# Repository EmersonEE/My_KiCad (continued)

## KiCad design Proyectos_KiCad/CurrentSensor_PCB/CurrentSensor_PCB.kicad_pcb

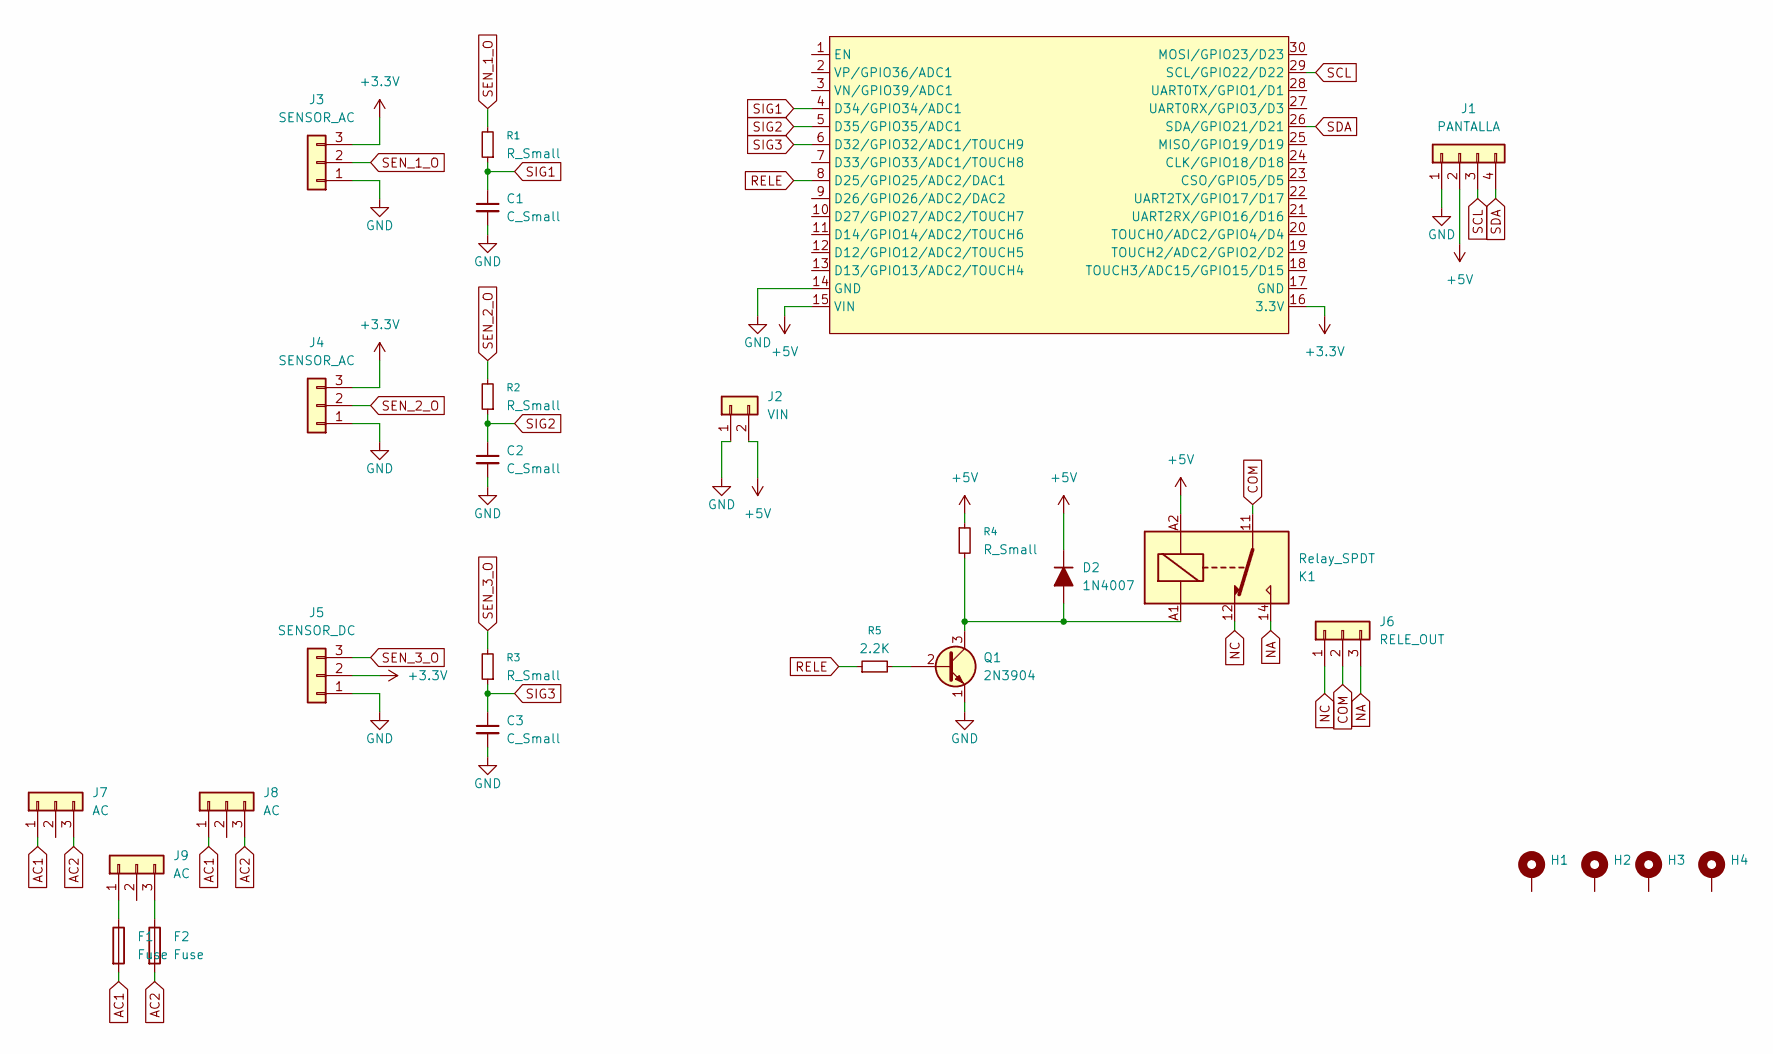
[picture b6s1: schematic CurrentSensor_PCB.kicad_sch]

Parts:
C1, C2, C3: C_Small; C_Disc_D3.8mm_W2.6mm_P2.50mm
D2: 1N4007; D_DO-41_SOD81_P7.62mm_Horizontal
F1, F2: Fuse; Fuseholder5x20_horiz_open_inline_Type-I
H1, H2, H3, H4: MountingHole_3.2mm_M3_Pad_Via
J1: PANTALLA; Molex_KK-254_AE-6410-04A_1x04_P2.54mm_Vertical
J2: VIN; TerminalBlock_Phoenix_MKDS-1,5-2-5.08_1x02_P5.08mm_Horizont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
J3, J4: SENSOR_AC; Molex_KK-254_AE-6410-03A_1x03_P2.54mm_Vertical
J5: SENSOR_DC; PinHeader_1x03_P2.54mm_Vertical
J6: RELE_OUT; TerminalBlock_Phoenix_MKDS-1,5-3-5.08_1x03_P5.08mm_Horizont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
J7, J8, J9: AC; TerminalBlock_Phoenix_MKDS-1,5-3-5.08_1x03_P5.08mm_Horizont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
K1: Relay_SPDT; Relay_SPDT_Finder_36.11
Q1: 2N3904; TO-92_Inline_Wide_EBC
R1, R2, R3, R4: R_Small; 2.2K
R5: 2.2K
U1: ESP32_DevKit_V1_DOIT; ESP32_DEVKIT_V1_E32

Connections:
+3.3V: J3.3, J4.3, J5.2, U1.16 (3.3V)
+5V: D2.1 (K), J1.2, J2.2, K1.A2, R4.1, U1.15 (VIN)
AC1: F1.2, J7.1, J8.1
AC2: F2.2, J7.3, J8.3
COM: J6.2, K1.11
GND: C1.2, C2.2, C3.2, J1.1, J2.1, J3.1, J4.1, J5.1, Q1.1 (E), U1.14 (GND)
NA: J6.3, K1.14
NC: J6.1, K1.12
unnamed: D2.2 (A), K1.A1, Q1.3 (C), R4.2
unnamed: F1.1, J9.1
unnamed: F2.1, J9.3
unnamed: Q1.2 (B), R5.2
RELE: R5.1, U1.8 (D25/GPIO25/ADC2/DAC1)
SCL: J1.3, U1.29 (SCL/GPIO22/D22)
SDA: J1.4, U1.26 (SDA/GPIO21/D21)
SEN_1_O: J3.2, R1.2
SEN_2_O: J4.2, R2.2
SEN_3_O: J5.3, R3.2
SIG1: C1.1, R1.1, U1.4 (D34/GPIO34/ADC1)
SIG2: C2.1, R2.1, U1.5 (D35/GPIO35/ADC1)
SIG3: C3.1, R3.1, U1.6 (D32/GPIO32/ADC1/TOUCH9)

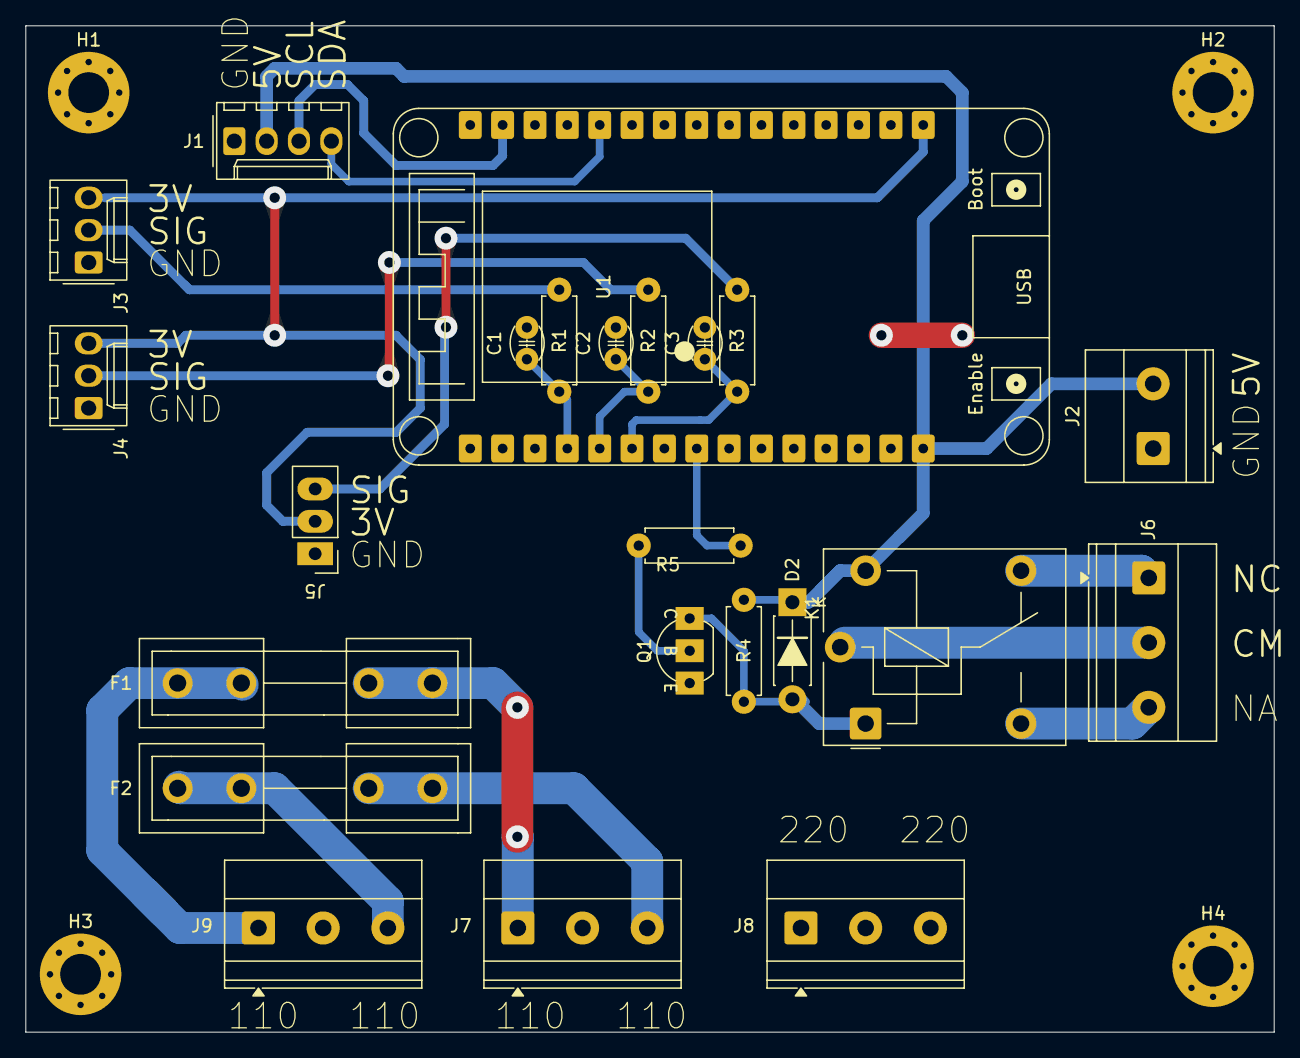
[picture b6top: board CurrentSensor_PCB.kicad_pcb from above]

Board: 2 copper layers, 98.0 x 79.0 mm, 27 parts (0 on the bottom side), 21 nets.
